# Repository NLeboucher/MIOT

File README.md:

# Introduction
# Abstract
In recent years, there has been a growing interest in developing new propulsion technologies that do not rely on fossil fuels. One such technology is ion propulsion, which uses electric fields to accelerate ions to generate thrust. While ion thrusters have been used primarily in space, recent studies have shown that they can also be useful on Earth, replacing conventional propellers in certain applications. This tutorial will provide an overview of the theory of ion propulsion, a brief history of its development, and a step-by-step guide to building a low-power ion thruster using 3D printing, PCB milling, and soldering skills.

# Context
Inspired by the [Plasma Channel](https://www.youtube.com/watch?v=nrEBoPYS4ns), this project focuses on using ion thruster technology to produce wind for the AOI project and replace its propellers. While most ion thrusters are used in space, there are already multiple ion thrusters made for Earth use cases, such as the MIT plane and Roswell flight, which rely on high tensions of + and -80kv.

# Overview of Ion Propulsion
Ion propulsion is a type of electric propulsion that uses electric fields to accelerate ions to generate thrust. Ion thrusters are used in space to provide propulsion for spacecraft, and they are also used on Earth for applications such as attitude control and station-keeping. Ion thrusters are different from conventional chemical rockets in that they do not use propellant to generate thrust. Instead, they use electric fields to accelerate ions to produce thrust. This is similar to how a Tesla coil produces a spark, but instead of using a spark gap, ion thrusters use an electric field to accelerate ions to produce thrust. Ion thrusters are also different from conventional electric thrusters in that they do not use a propellant to generate thrust. Instead, they use electric fields to accelerate ions to produce thrust. This is similar to how a Tesla coil produces a spark, but instead of using a spark gap, ion thrusters use an electric field to accelerate ions to produce thrust. Ion thrusters are also different from conventional electric thrusters in that they do not use a propellant to generate thrust. Instead, they use electric fields to accelerate ions to produce thrust. This is similar to how a Tesla coil produces a spark, but instead of using a spark gap, ion thrusters use an electric field to accelerate ions to produce thrust. Ion thrusters are also different from conventional electric thrusters in that they do not use a propellant to generate thrust. Instead, they use electric fields to accelerate ions to produce thrust. This is similar to how a Tesla coil produces a spark, but instead of using a spark gap, ion thrusters use an electric field to accelerate ions to produce thrust. Ion thrusters are also different from conventional electric thrusters in that they do not use a propellant to generate thrust. Instead, they use electric fields to accelerate ions to produce thrust. This is similar to how a Tesla coil produces a spark, but instead of using a spark gap, ion thrusters use an electric field to accelerate ions to produce thrust. Ion thrusters are also different from conventional electric thrusters in that they do not use a propellant to generate thrust. Instead, they use electric fields to accelerate ions to produce thrust. This is similar to how a Tesla coil produces a spark, but instead of using a spark gap, ion thrusters use an electric field to accelerate ions to produce thrust. Ion thrusters are also different from conventional electric thrusters in that they do not use a propellant to generate thrust. Instead,

# State of the Art

The concept of ion propulsion was first proposed in 1906 by Robert Goddard, but it was not until the 1960s that the first ion thrusters were developed for space applications. The first successful ion thrusters were developed by NASA's Glenn Research Center in the late 1960s, and these early designs paved the way for further developments in ion propulsion technology.[^3]
One of the earliest ion thrusters was the SERT-1 thruster, which was developed by NASA in the 1960s. This thruster used mercury as a propellant and demonstrated the basic principles of ion propulsion. However, it had a low thrust-to-weight ratio and limited operating life.[^3]
In the 1970s, NASA developed the NSTAR ion thruster, which used xenon gas as a propellant. This thruster was much more efficient than the earlier designs and had a higher thrust-to-weight ratio. The NSTAR thruster was first used on the Deep Space 1 mission in 1998 and has since been used on several other spacecraft, including NASA's Dawn mission to study Vesta and Ceres.[^3]
In the 1990s, the European Space Agency (ESA) developed the High-Efficiency Multistage Plasma Thruster (HEMP-T), which used a different type of ionization process than earlier designs. The HEMP-T thruster was more efficient and had a longer operating life than earlier designs.[^3]
In the early 2000s, NASA developed the Evolutionary Xenon Thruster (NEXT), which was based on the NSTAR design but had several improvements. The NEXT thruster had a higher thrust-to-weight ratio and was more efficient than the NSTAR thruster. It has since been used on several missions,[^4] including NASA's OSIRIS-REx mission to study the asteroid Bennu.
One of the most recent developments in ion propulsion is the Dual-Stage 4-Grid (DS4G) ion thruster, which was developed by NASA's Jet Propulsion Laboratory (JPL) in the early 2010s. The DS4G thruster is more efficient and has a higher thrust-to-weight ratio than earlier designs. It has been tested on several spacecraft, including NASA's DART mission to deflect an asteroid and the Psyche mission to study a metal-rich asteroid.[^5]
The Micro-Cathode Arc Thruster (µCAT) has demonstrated several impressive performance characteristics for its size and power requirements.
The specific impulse (a measure of how efficiently a thruster uses propellant) of the µCAT has been measured at around 1600 seconds for oxygen propellant, which is higher than other low-power thrusters like cold gas thrusters and electrostatic thrusters.
The maximum thrust produced by the µCAT has been measured at around 40 micro-Newtons, which is enough to provide attitude control and station-keeping for small spacecraft.
However, despite the many improvements made in ion propulsion technology over the years, there are still several challenges that need to be addressed. One of the main challenges is the high power requirements of ion thrusters, which limits their use on smaller spacecraft. 
The MIT has made a plane as well as a buisness Roswell flight. They rely on high tensions(+ and -80kv). [^1] [^2]

This project will focus on using this technology to produce wind for the AOI project, to replace its propellers and help miniaturize the project. 

# Building a Low-Power Ion Thruster

To build a low-power ion thruster, you will need to 3D print 8 cathodes and anodes, and solder a circuit board. Here's a step-by-step guide:

1    3D print 4 arcs.

2    Fix the copper cables onto the cathodes using hot glue to make two cathodes.

3    Glue the arcs onto the aluminum foil and fix them on a plastic board to make two anodes.

4    Mill a circuit board using the provided schematic.

5    Solder the components onto the circuit board, including the resistors and LED.

6    Connect the circuit board to the cathodes and anodes using electronic cables.

7    Apply high voltage to the anodes and cathodes to create the ion wind.

Note: Be careful when working with high voltages!

# Conclusion

Ion thrusters offer a promising alternative to conventional propulsion systems, particularly for in-space maneuvers. However, recent studies have also shown their potential for Earth-based applications. This tutorial has provided an overview of ion propulsion, a brief history of its development, and a step-by-step guide to building a low-power ion thruster using 3D printing, PCB milling, and soldering skills. While the process may require some trial and error, particularly when drilling the aluminum sheets to make the anodes, this project demonstrates the possibilities of ion thruster technology for Earth-based applications and its potential to revolutionize propulsion systems.

# Sources:
[^1]: https://www.youtube.com/watch?v=TeJyMbSSUIc

[^2]: https://www.youtube.com/watch?v=UGM4JXVB5FM

[^3]:    Goebel, D. M., & Katz, I. (2008). Fundamentals of electric propulsion: ion and Hall thrusters. John Wiley & Sons.

[^4]:    JPL. (2021). Dual-Stage 4-Grid (DS4G) Ion Thruster. Retrieved from https://www.jpl.nasa.gov/news/dual-stage-4-grid-ds4g-ion-thruster

[^5]:    NASA. (2021). Ion Propulsion. Retrieved from https://www.nasa.gov/centers/glenn/about/fs21grc.html

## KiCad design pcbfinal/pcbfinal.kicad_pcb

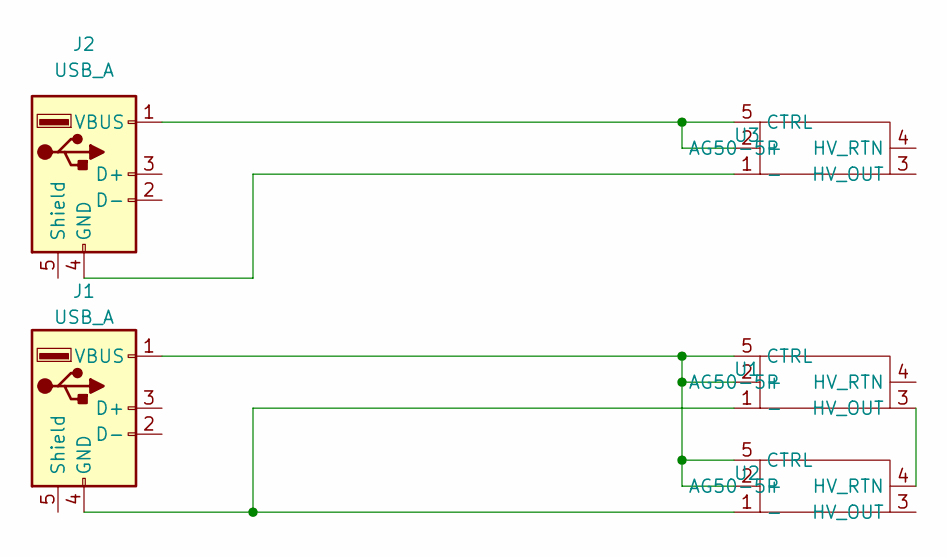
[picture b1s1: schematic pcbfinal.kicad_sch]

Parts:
J1, J2: USB_A; USB_A_CONNFLY_DS1095-WNR0
U1, U2, U3: AG50-5P

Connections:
unnamed: J1.1 (VBUS), U1.2 (+), U1.5 (CTRL), U2.2 (+), U2.5 (CTRL)
unnamed: J1.4 (GND), U1.1 (-), U2.1 (-)
unnamed: J2.1 (VBUS), U3.2 (+), U3.5 (CTRL)
unnamed: J2.4 (GND), U3.1 (-)
unnamed: U1.3 (HV_OUT), U2.4 (HV_RTN)

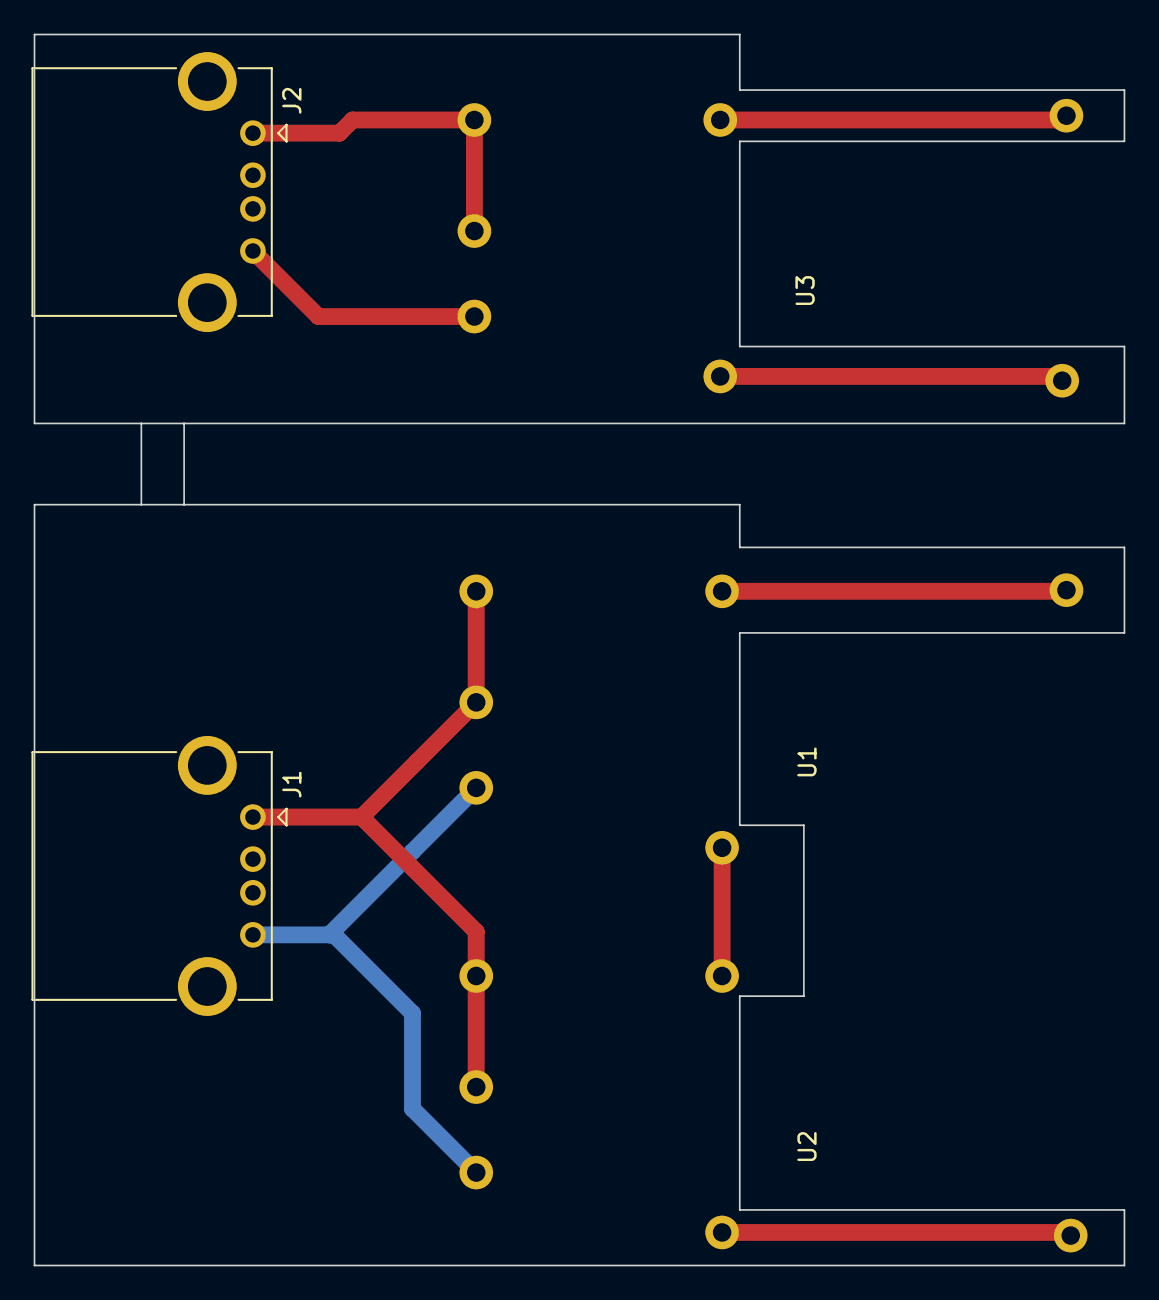
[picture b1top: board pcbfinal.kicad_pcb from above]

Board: 2 copper layers, 64.8 x 73.2 mm, 5 parts (0 on the bottom side), 5 nets.

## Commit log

2023-03-26 pcbs
2023-03-27 added 3d files
2023-03-27 added README
2023-03-28 added more 2/3d files for compatibility
